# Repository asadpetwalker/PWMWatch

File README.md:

# PWMWatch
# What My Project Is
My project is a watch using the CrystalFontz CFAL12856A0 transparent display, the STM32WB50CGU5 mcu, and the RV3028-C7 RTC.

# Why I made my project
The electronics of watches are like really cool, and I don't see anyone actually talking about them more. I smashed a broken smart watch with a hammer, and inside there was a bunch of electronics that were really cool when I desoldered them. Additionally, the display I found, the CrystalFontz CFAL12856A0 is really cool, and I wanted to combine these two things to make a really cool watch that also focuses on the electronics.

# Pictures

# BOM

| Name | Purpose | Quantity | Total Cost (USD) | Link | Distributor |
|------|---------|----------|------------------|------|-------------|
| PCB + Stencil | PCB |  | 21.55 |  | JLCPCB |
| MBR0530TPMSCT-ND | DIODE SCHOTTKY 30V 500MA SOD123 | 2 | 0.30 | https://www.digikey.com/en/products/detail/mcc-micro-commercial-components/MBR0530-TP/717251 | Digikey |
| RB521S30T1GOSCT-ND | DIODE SCHOTTKY 30V 200MA SOD523 | 2 | 0.30 | https://www.digikey.com/en/products/detail/onsemi/RB521S30T1G/920292 | Digikey |
| B130LAW-FDICT-ND | DIODE SCHOTTKY 30V 1A SOD123 | 2 | 0.70 | https://www.digikey.com/en/products/detail/diodes-incorporated/B130LAW-7-F/725013 | Digikey |
| 36-2994-ND | BATTERY RETAINER COIN 4.8MM SMD | 2 | 0.60 | https://www.digikey.com/en/products/detail/keystone-electronics/2994/2137865 | Digikey |
| 2073-MEM2061-01-188-00-ACT-ND | CONN MICRO SD CARD R/A SMD | 2 | 2.24 | https://www.digikey.com/en/products/detail/gct/MEM2061-01-188-00-A/9859612 | Digikey |
| 108-KMR211GLFSCT-ND | SWITCH TACTILE SPST-NO 0.05A 32V | 4 | 2.44 | https://www.digikey.com/en/products/detail/c-k/KMR211G-LFS/550475 | Digikey |
| 308-1969-1-ND | FIXED IND 10UH 670MA 440 MOHM | 4 | 2.32 | https://www.digikey.com/en/products/detail/sumida-america-inc/CDRH3D14-HPNP-100NC/3946967 | Digikey |
| 311-1140-1-ND | CAP CER 0.1UF 50V X7R 0805 | 40 | 0.48 | https://www.digikey.com/en/products/detail/yageo/CC0805KRX7R9BB104/302874 | Digikey |
| 587-1441-1-ND | CAP CER 4.7UF 10V X5R 0603 | 10 | 0.20 | https://www.digikey.com/en/products/detail/taiyo-yuden/LMK107BJ475KA-T/1004029 | Digikey |
| 311-2.7KGRCT-ND | RES 2.7K OHM 5% 1/10W 0603 | 10 | 0.08 | https://www.digikey.com/en/products/detail/yageo/RC0603JR-072K7L/726735 | Digikey |
| 311-100KHRCT-ND | RES 100K OHM 1% 1/10W 0603 | 25 | 0.14 | https://www.digikey.com/en/products/detail/yageo/RC0603FR-07100KL/726889 | Digikey |
| 311-47.0KHRCT-ND | RES 47K OHM 1% 1/10W 0603 | 10 | 0.08 | https://www.digikey.com/en/products/detail/yageo/RC0603FR-0747KL/727253 | Digikey |
| 296-50511-1-ND | UNIDIR PRECISION SURGE DIODE | 3 | 2.85 | https://www.digikey.com/en/products/detail/texas-instruments/TVS1400DRVR/8566097 | Digikey |
| 2195-RV-3028-C8-32.768KHZ-1PPM-TA-QCCT-ND | IC RTC CLK/CALENDAR I2C 8SON | 1 | 3.05 | https://www.digikey.com/en/products/detail/micro-crystal-ag/RV-3028-C8-32-768KHZ-1PPM-TA-QC/26226350 | Digikey |
| AP3012KTR-G1DICT-ND | IC REG BOOST ADJ 500MA SOT23-5 | 2 | 0.58 | https://www.digikey.com/en/products/detail/diodes-incorporated/AP3012KTR-G1/4470846 | Digikey |
| MAX17048G+T10CT-ND | IC BATT MON LI-ION 1CELL 8TDFN | 1 | 4.10 | https://www.digikey.com/en/products/detail/analog-devices-inc-maxim-integrated/MAX17048G-T10/3758921 | Digikey |
| MCP73831T-2DCI/OTCT-ND | IC BATT CNTL LI-ION 1CEL SOT23-5 | 2 | 1.52 | https://www.digikey.com/en/products/detail/microchip-technology/MCP73831T-2DCI-OT/964305 | Digikey |
| AS5600-ASOTCT-ND | IC SENSOR MAG ROTARY 12BIT 8SOIC | 1 | 3.09 | https://www.digikey.com/en/products/detail/ams-osram-usa-inc/AS5600-ASOT/4914338 | Digikey |
| 3147-B1931NG--20D001114U1930CT-ND | LED GREEN DIFFUSED 0603 SMD | 2 | 0.54 | https://www.digikey.com/en/products/detail/harvatek-corporation/B1931NG-20D001114U1930/15861262 | Digikey |
| BSS83PH6327XTSA1CT-ND | MOSFET P-CH 60V 330MA SOT23-3 | 2 | 0.88 | https://www.digikey.com/en/products/detail/infineon-technologies/BSS83PH6327XTSA1/2783473 | Digikey |
| P19095CT-ND | SWITCH TACTILE SPST-NO 0.05A 12V | 4 | 1.20 | https://www.digikey.com/en/products/detail/panasonic-industry/EVQ-9P701P/5250479 | Digikey |
| 2073-USB4105-GF-ACT-ND | CONN RCP USB2.0 TYP C 16P SMD RA | 4 | 3.12 | https://www.digikey.com/en/products/detail/gct/USB4105-GF-A/11198441 | Digikey |
| 455-1788-1-ND | CONN HEADER SMD 2POS 1MM | 3 | 1.17 | https://www.digikey.com/en/products/detail/jst-sales-america-inc/BM02B-SRSS-TB/926694 | Digikey |
| 2073-FFC2A32-24-TCT-ND | CONN FFC VERT 24POS 0.5MM SMD | 4 | 2.56 | https://www.digikey.com/en/products/detail/gct/FFC2A32-24-T/10656996 | Digikey |
| 469-1075-ND | MAGNET 0.236"D X 0.098"THICK CYL | 3 | 2.25 | https://www.digikey.com/en/products/detail/radial-magnets-inc/9049/6030786 | Digikey |
| 728-1088-ND | BATTERY SLVR OX 1.55V COIN 4.8MM | 2 | 6.10 | https://www.digikey.com/en/products/detail/seiko-instruments/SR421SW/7428808 | Digikey |
| 1528-1841-ND | BATTERY LITH-ION 3.7V 500MAH | 1 | 7.95 | https://www.digikey.com/en/products/detail/adafruit-industries-llc/1578/5054539 | Digikey |
| 478-3868-1-ND | CAP TANT 4.7UF 10% 16V 1206 | 10 | 2.11 | https://www.digikey.com/en/products/detail/kyocera-avx/TAJA475K016RNJ/1126796 | Digikey |
| 587-1300-1-ND | CAP CER 10UF 10V X5R 0805 | 10 | 0.16 | https://www.digikey.com/en/products/detail/taiyo-yuden/LMK212BJ106KG-T/930652 | Digikey |
| 311-10.0KHRCT-ND | RES 10K OHM 1% 1/10W 0603 | 25 | 0.14 | https://www.digikey.com/en/products/detail/yageo/RC0603FR-0710KL/726880 | Digikey |
| 311-5.10KHRCT-ND | RES 5.1K OHM 1% 1/10W 0603 | 10 | 0.07 | https://www.digikey.com/en/products/detail/yageo/RC0603FR-075K1L/727268 | Digikey |
| 311-470GRCT-ND | RES 470 OHM 5% 1/10W 0603 | 10 | 0.07 | https://www.digikey.com/en/products/detail/yageo/RC0603JR-07470RL/726791 | Digikey |
| NCP1117LPST33T3GOSCT-ND | IC REG LINEAR 3.3V 1A SOT-223 | 2 | 0.74 | https://www.digikey.com/en/products/detail/onsemi/NCP1117LPST33T3G/2194024 | Digikey |
| 497-STM32WB50CGU5-ND | IC RF TXRX+MCU 802.15.4 48UFQFPN | 2 | 10.80 | https://www.digikey.com/en/products/detail/stmicroelectronics/STM32WB50CGU5/10673126 | Digikey |

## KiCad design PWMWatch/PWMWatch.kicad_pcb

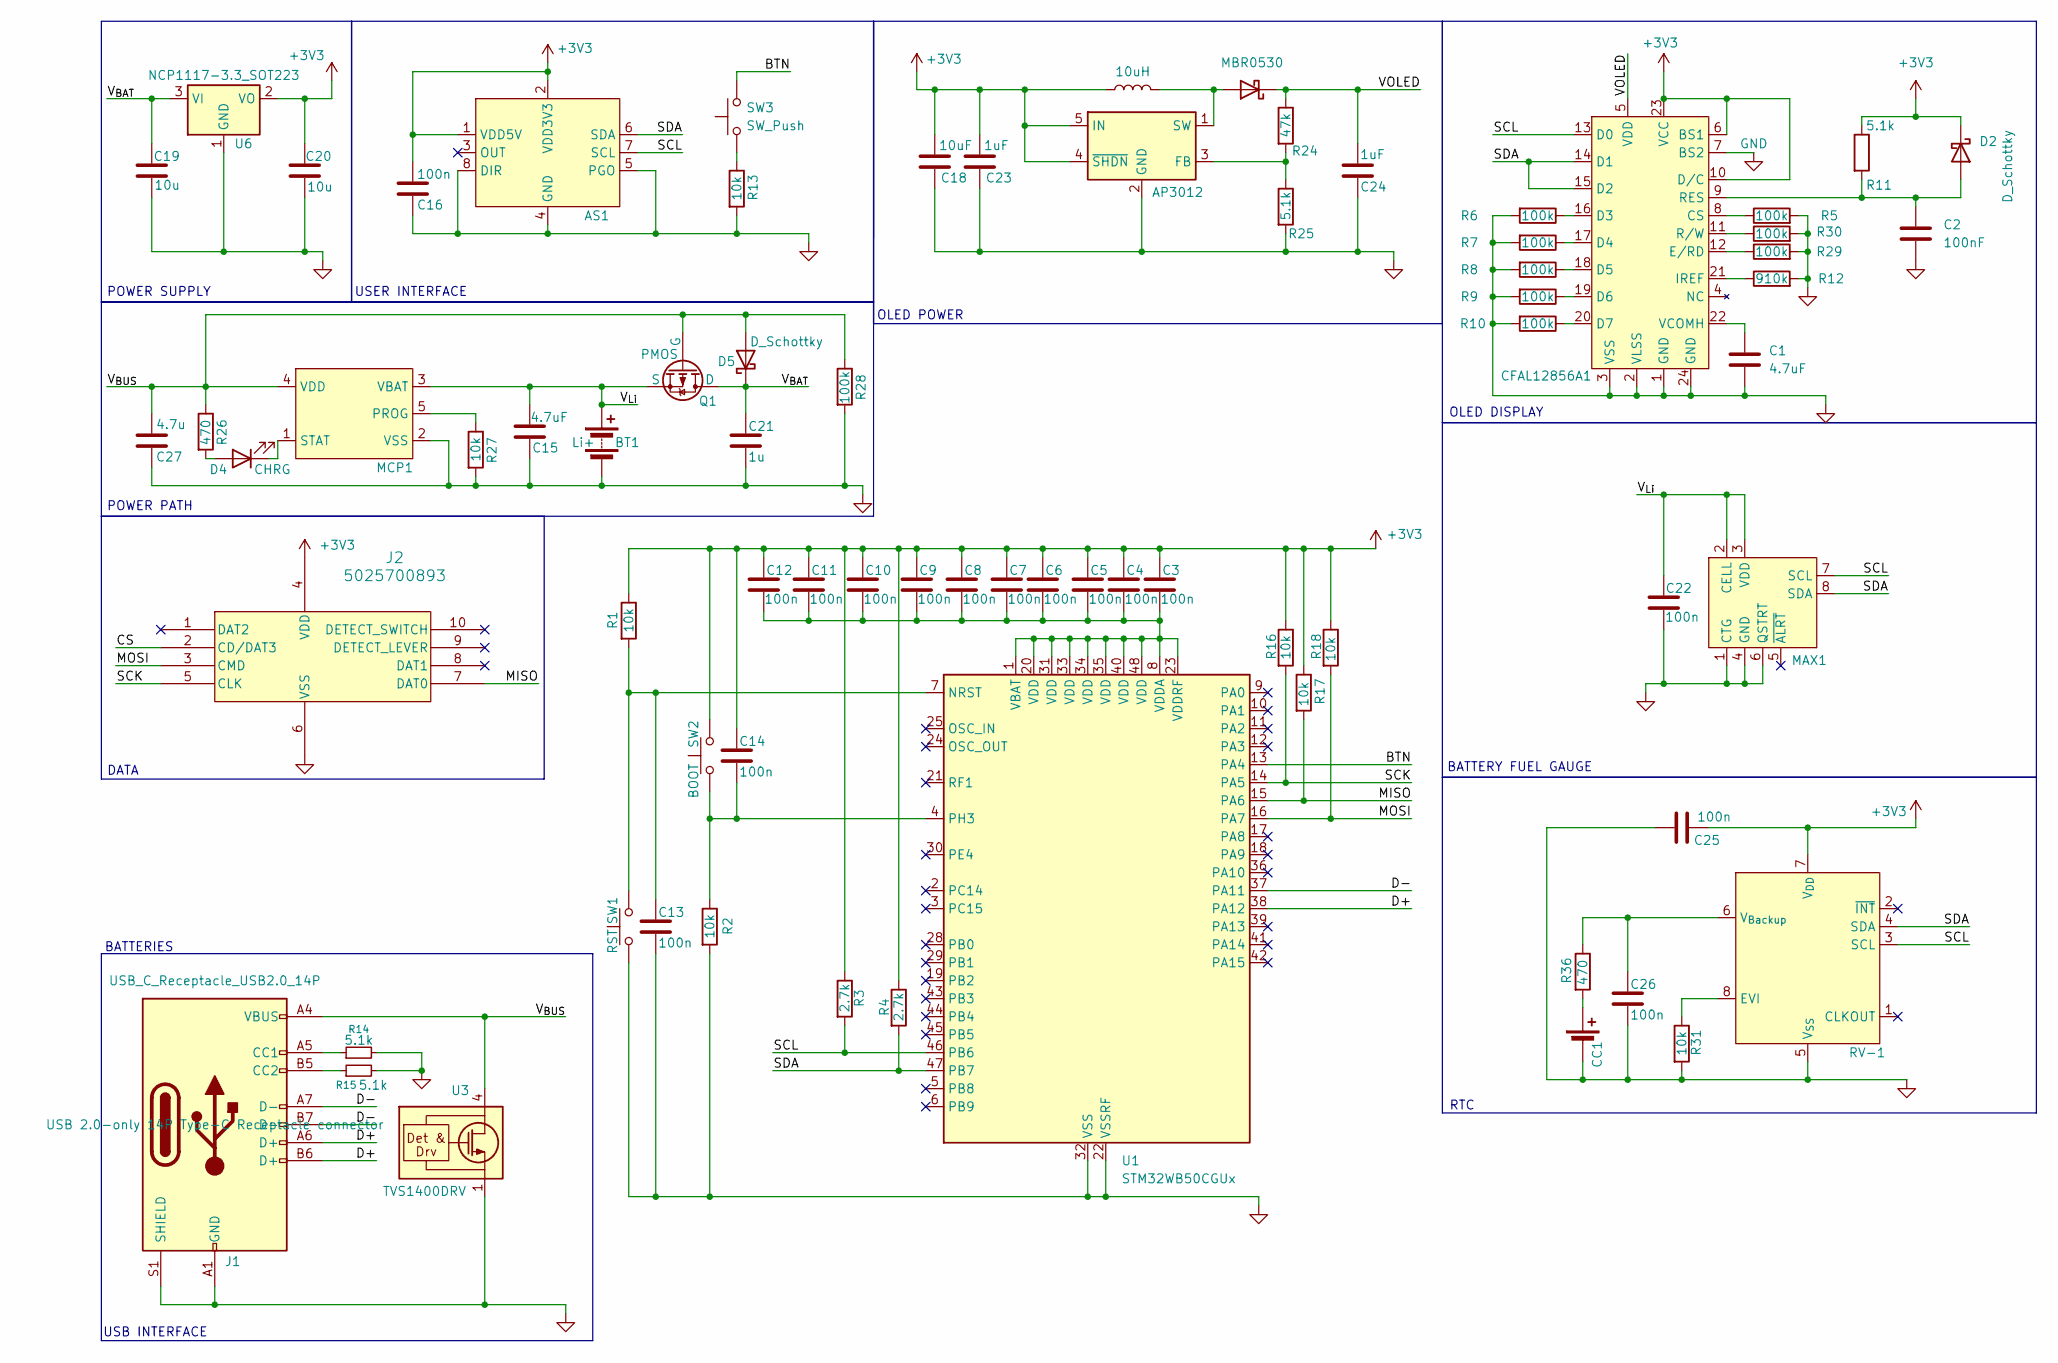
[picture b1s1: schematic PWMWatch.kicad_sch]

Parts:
AS1: SOIC-8_3.9x4.9mm_P1.27mm
BT1: Li+; CONN_BM02B-SRSS-TB_JST
C1: 4.7uF; C_1206_3216Metric
C2: 100nF; C_0805_2012Metric
C3, C4, C5, C6, C7, C8, C9, C10, C11, C12, C13, C14, C16, C22, C25, C26: 100n; C_0805_2012Metric
C15: 4.7uF; C_0603_1608Metric
C18: 10uF; C_0805_2012Metric
C19, C20: 10u; C_0805_2012Metric
C21: 1u; C_0805_2012Metric
C23, C24: 1uF; C_0805_2012Metric
C27: 4.7u; C_0603_1608Metric
CC1: Battery_Cell; BAT_2994
CFAL12856A1: GCT_FFC2A32-24-T
D2: D_Schottky; D_SOD-523
D4: CHRG; LED_0603_1608Metric
D5: D_Schottky; D_SOD-123
D6: MBR0530; D_SOD-123
J1: USB_C_Receptacle_USB2.0_14P; USB_C_Receptacle_GCT_USB4105-xx-A_16P_TopMnt_Horizontal
J2: 5025700893; MOLEX_5025700893
L2: 10uH; CDRH3D14HPNP100NC
MAX1: TDFN-8-1EP_2x2mm_P0.5mm_EP0.8x1.2mm
MCP1: SOT-23-5
Q1: PMOS; SOT-23-3
R1, R2: 10k; C_0603_1608Metric
R3, R4: 2.7k; C_0603_1608Metric
R5, R6, R7, R8, R9, R10, R28, R29, R30: 100k; R_0603_1608Metric
R11, R14, R15, R25: 5.1k; R_0603_1608Metric
R12: 910k; R_0603_1608Metric
R13, R16, R17, R18, R27, R31: 10k; R_0603_1608Metric
R24: 47k; R_0603_1608Metric
R26, R36: 470; R_0603_1608Metric
RV-1: IC_RV-3028-C8-32.768KHZ-1PPM-TA-QC
SW1: RST; SW_Push_1P1T_NO_CK_KMR2
SW2: BOOT; SW_Push_1P1T_NO_CK_KMR2
SW3: SW_Push; SW_EVQ-P7A01P
U1: STM32WB50CGUx; QFN-48-1EP_7x7mm_P0.5mm_EP5.6x5.6mm
U2: AP3012; SC-74A-5_1.55x2.9mm_P0.95mm
U3: TVS1400DRV; WSON-6-1EP_2x2mm_P0.65mm_EP1x1.6mm
U6: NCP1117-3.3_SOT223; SOT-223-3_TabPin2

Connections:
+3V3: AS1.1 (VDD5V), AS1.2 (VDD3V3), C3.1, C4.1, C5.1, C6.1, C7.1, C8.1, C9.1, C10.1, C11.1, C12.1, C14.1, C16.1, C18.1, C20.2, C23.1, C25.2, CFAL12856A1.6 (BS1), CFAL12856A1.10 (D/C), CFAL12856A1.23 (VCC), D2.1 (K), J2.4 (VDD), L2.1, R1.1, R3.1, R4.1, R11.1, R16.1, R17.1, R18.1, RV-1.7 (V_{DD}), SW2.2, U2.4 (~SHDN), U2.5 (IN), U6.2 (VO)
/BTN: SW3.2, U1.13 (PA4)
/CS: J2.2 (CD/DAT3)
/D+: J1.A6 (D+), J1.B6 (D+), U1.38 (PA12)
/D-: J1.A7 (D-), J1.B7 (D-), U1.37 (PA11)
/MISO: J2.7 (DAT0), R17.2, U1.15 (PA6)
/MOSI: J2.3 (CMD), R18.2, U1.16 (PA7)
/SCK: J2.5 (CLK), R16.2, U1.14 (PA5)
/SCL: AS1.7 (SCL), CFAL12856A1.13 (D0), MAX1.7 (SCL), R3.2, RV-1.3 (SCL), U1.46 (PB6)
/SDA: AS1.6 (SDA), CFAL12856A1.14 (D1), CFAL12856A1.15 (D2), MAX1.8 (SDA), R4.2, RV-1.4 (SDA), U1.47 (PB7)
/VOLED: C24.1, CFAL12856A1.5 (VDD), D6.1 (K), R24.1
/V_{BAT}: C19.2, C21.1, D5.1 (K), Q1.1 (D), U6.3 (VI)
/V_{BUS}: C27.1, D5.2 (A), J1.A4 (VBUS), J1.A9 (VBUS), J1.B4 (VBUS), J1.B9 (VBUS), MCP1.4 (VDD), Q1.2 (G), R26.1, R28.1, U3.4 (IN), U3.5 (IN), U3.6 (IN)
/V_{Li}: BT1.1 (+), C15.1, C22.2, MAX1.2 (CELL), MAX1.3 (VDD), MCP1.3 (VBAT), Q1.3 (S)
GND: AS1.4 (GND), AS1.5 (PGO), AS1.8 (DIR), BT1.2 (-), C1.2, C2.2, C13.1, C15.2, C16.2, C18.2, C19.1, C20.1, C21.2, C22.1, C23.2, C24.2, C25.1, C26.2, C27.2, CC1.2 (-), CFAL12856A1.1 (GND), CFAL12856A1.2 (VLSS), CFAL12856A1.3 (VSS), CFAL12856A1.7 (BS2), CFAL12856A1.24 (GND), J1.A1 (GND), J1.A12 (GND), J1.B1 (GND), J1.B12 (GND), J1.S1 (SHIELD), J2.6 (VSS), MAX1.1 (CTG), MAX1.4 (GND), MAX1.6 (QSTRT), MCP1.2 (VSS), R2.2, R5.2, R6.2, R7.2, R8.2, R9.2, R10.2, R12.2, R13.2, R14.2, R15.2, R25.2, R27.2, R28.2, R29.2, R30.2, R31.2, RV-1.5 (V_{SS}), SW1.1, U1.22 (VSSRF), U1.32 (VSS), U1.49 (VSS), U2.2 (GND), U3.1 (GND), U3.2 (GND), U3.3 (GND), U3.7 (GND), U6.1 (GND)
unnamed: CC1.1 (+), R36.2
unnamed: CFAL12856A1.8 (CS), R5.1
unnamed: CFAL12856A1.16 (D3), R6.1
unnamed: CFAL12856A1.17 (D4), R7.1
unnamed: CFAL12856A1.18 (D5), R8.1
unnamed: CFAL12856A1.19 (D6), R9.1
unnamed: CFAL12856A1.20 (D7), R10.1
unnamed: CFAL12856A1.12 (E/RD), R29.1
unnamed: CFAL12856A1.21 (IREF), R12.1
unnamed: C2.1, CFAL12856A1.9 (RES), D2.2 (A), R11.2
unnamed: CFAL12856A1.11 (R/W), R30.1
unnamed: C1.1, CFAL12856A1.22 (VCOMH)
unnamed: D4.2 (A), R26.2
unnamed: D4.1 (K), MCP1.1 (STAT)
unnamed: D6.2 (A), L2.2, U2.1 (SW)
unnamed: J1.A5 (CC1), R14.1
unnamed: J1.B5 (CC2), R15.1
unnamed: MCP1.5 (PROG), R27.1
unnamed: R13.1, SW3.1
unnamed: R31.1, RV-1.8 (EVI)
unnamed: C26.1, R36.1, RV-1.6 (V_{Backup})
unnamed: C13.2, R1.2, SW1.2, U1.7 (NRST)
unnamed: C14.2, R2.1, SW2.1, U1.4 (PH3)
unnamed: C3.2, C4.2, C5.2, C6.2, C7.2, C8.2, C9.2, C10.2, C11.2, C12.2, U1.1 (VBAT), U1.8 (VDDA), U1.20 (VDD), U1.23 (VDDRF), U1.31 (VDD), U1.33 (VDD), U1.34 (VDD), U1.35 (VDD), U1.40 (VDD), U1.48 (VDD)
unnamed: R24.2, R25.1, U2.3 (FB)

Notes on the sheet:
OLED POWER
POWER SUPPLY
RTC
POWER PATH
USB INTERFACE
BATTERY FUEL GAUGE
DATA
BATTERIES
USER INTERFACE
OLED DISPLAY

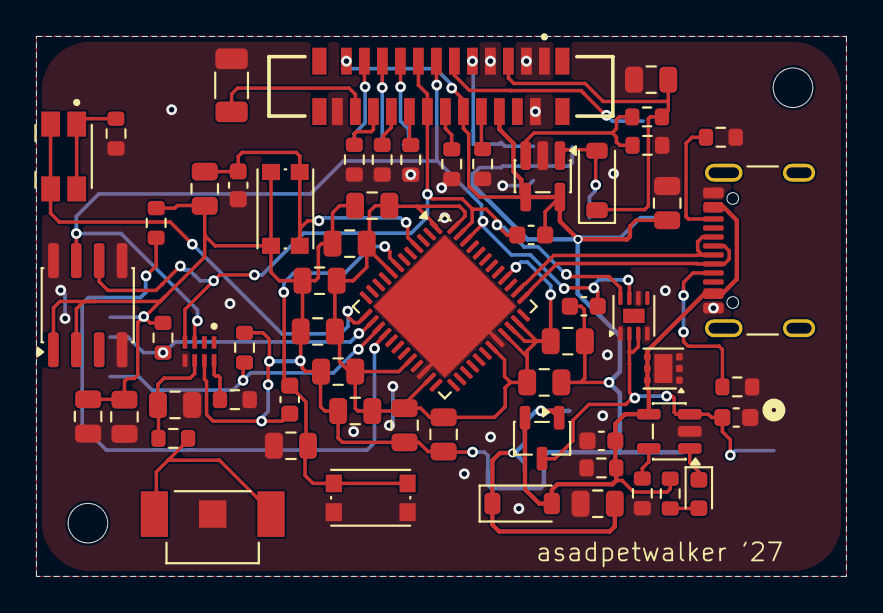
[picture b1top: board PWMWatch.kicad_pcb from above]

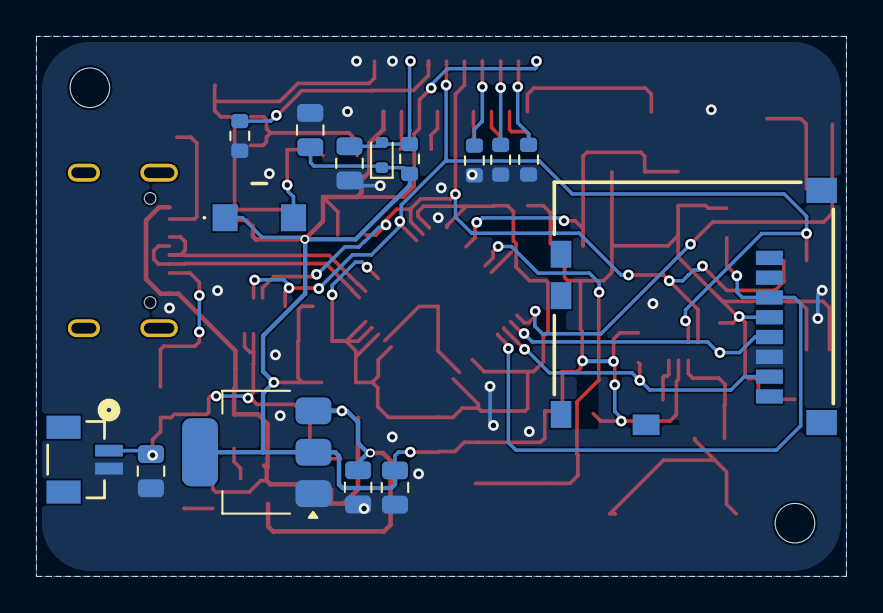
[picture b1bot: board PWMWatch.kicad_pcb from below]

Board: 2 copper layers, 45.0 x 30.0 mm, 75 parts (15 on the bottom side), 39 nets.

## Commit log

2026-03-05 Started schematic
2026-03-06 Added RTC
2026-03-21 magnetic encoder + buttons + organization of schematic
2026-03-22 footprints
2026-03-24 placements + fixed all the wrong footprints
2026-04-02 pcb done 4th time
2026-04-05 all the stuff done
2026-04-05 readme
2026-04-05 readme + csv
